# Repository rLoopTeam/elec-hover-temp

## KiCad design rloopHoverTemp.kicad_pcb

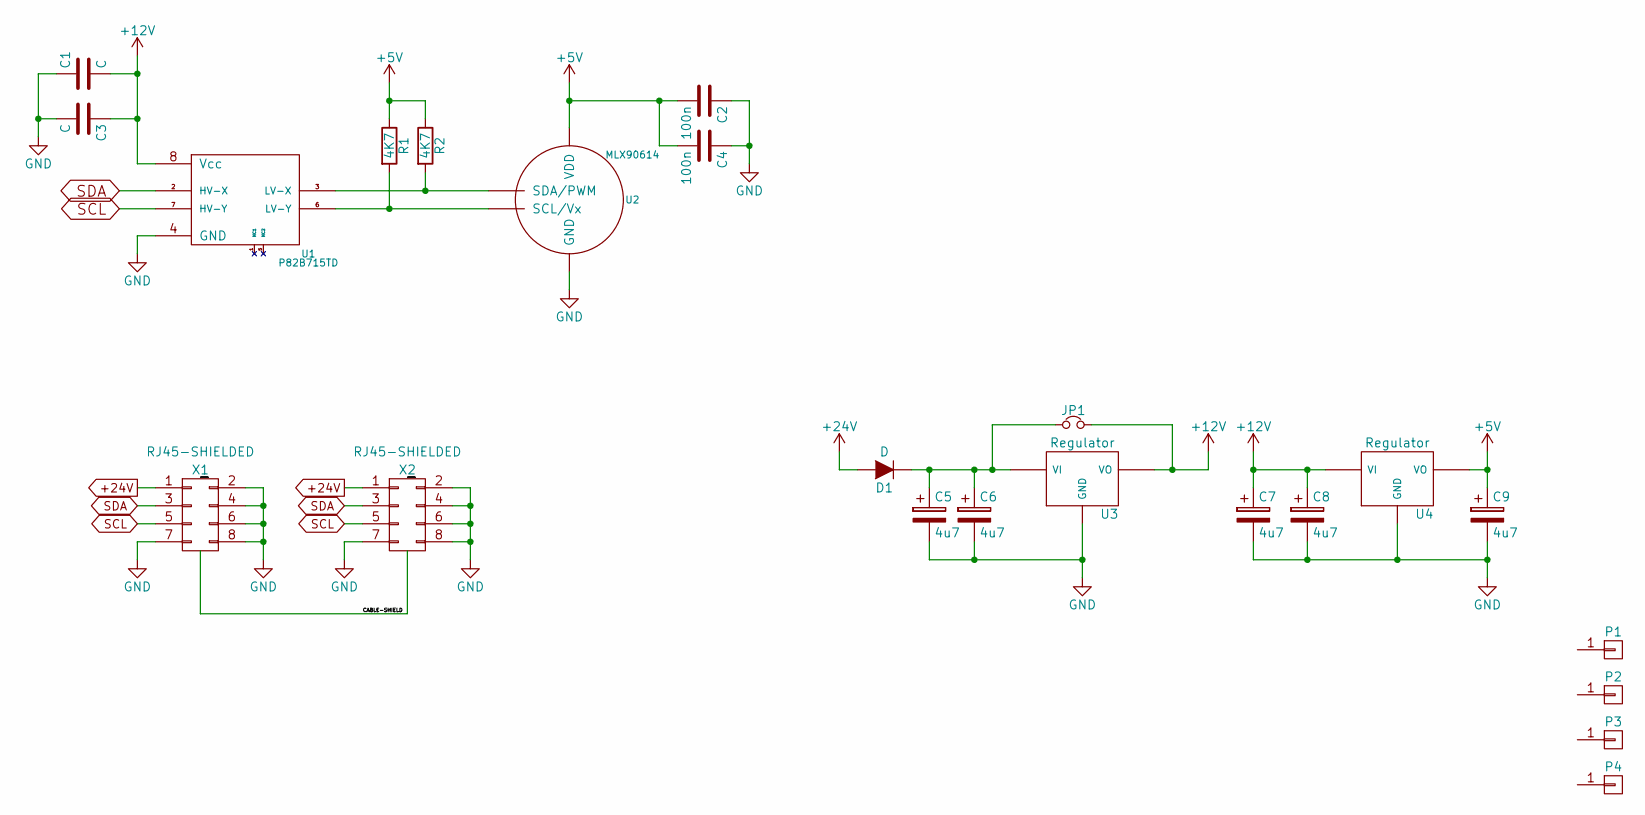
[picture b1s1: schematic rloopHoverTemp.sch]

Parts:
C1, C3: C; C_0603_HandSoldering
C2, C4: 100n; C_0603_HandSoldering
C5, C6, C7, C8, C9: 4u7; C_1206_HandSoldering
D1: D; SOD-123
JP1: Jumper_NC_Small; SOLDERJUMPER
P1, P2, P3, P4: CONN_01X01; SCREWPAD-4-40
R1, R2: 4K7; R_0603_HandSoldering
U1: P82B715TD; SOIC-8_3.9x4.9mm_Pitch1.27mm
U2: MLX90614; TO39
U3, U4: Regulator; SOT89-3-VREG
X1, X2: RJ45-SHIELDED; RJ45-TE-5558342-1

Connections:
+5V: C2.2, C4.2, C9.1, R1.1, R2.1, U2.3 (VDD), U4.VO
+12V: C1.2, C3.1, C7.1, C8.1, JP1.2, U1.8 (Vcc), U3.VO, U4.VI
+24V: D1.2 (A), X1.1, X2.1
/CABLE-SHIELD: X1.SHLD (SHLD1), X2.SHLD (SHLD1)
GND: C1.1, C2.1, C3.2, C4.1, C5.2, C6.2, C7.2, C8.2, C9.2, U1.4 (GND), U2.4 (GND), U3.GND, U4.GND, X1.2, X1.4, X1.6, X1.7, X1.8, X2.2, X2.4, X2.6, X2.7, X2.8
unnamed: C5.1, C6.1, D1.1 (K), JP1.1, U3.VI
unnamed: R1.2, U1.6 (LV-Y), U2.1 (SCL/Vx)
unnamed: R2.2, U1.3 (LV-X), U2.2 (SDA/PWM)
SCL: U1.7 (HV-Y), X1.5, X2.5
SDA: U1.2 (HV-X), X1.3, X2.3

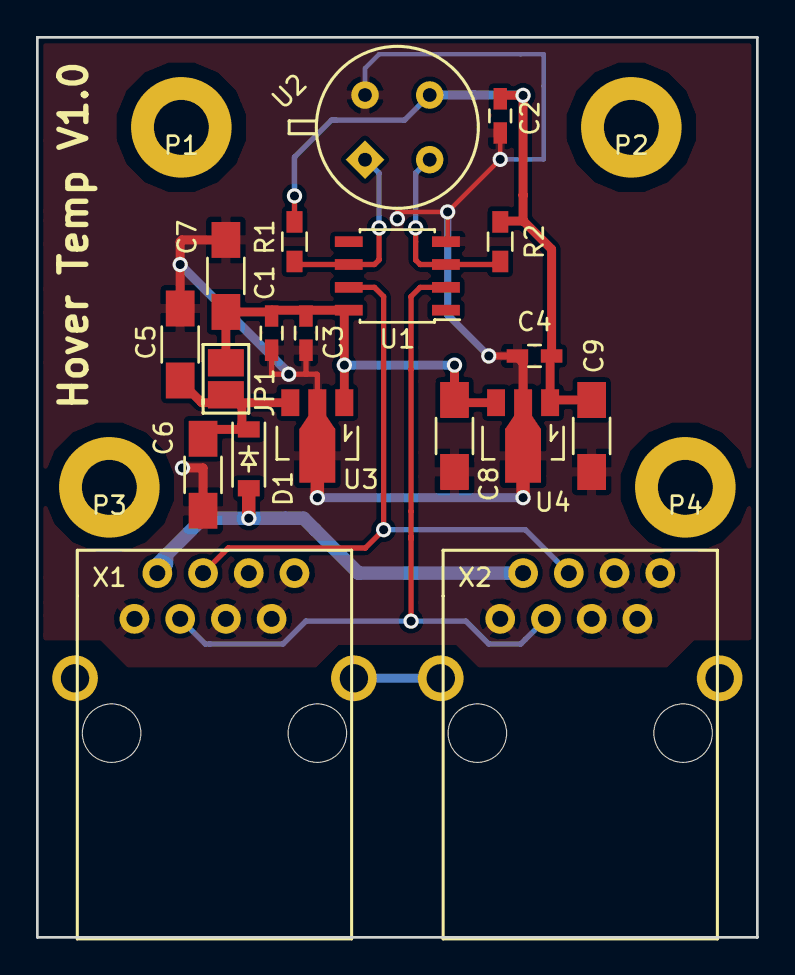
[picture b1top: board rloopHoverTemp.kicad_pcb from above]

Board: 2 copper layers, 40.0 x 50.0 mm, 23 parts (0 on the bottom side), 10 nets.

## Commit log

2016-05-17 first rev
2016-05-17 prelim layout
2016-05-17 more spacing for 24V, better route, gnd'd mnts
2016-05-17 split the grounds
2016-05-17 touchup, put some dimensions on there
2016-05-17 added reverse wiring protection diode
2016-05-21 complete redo with MLX sensor
2016-05-22 dual MNL connector version
2016-05-22 version with dual RJ45 connector
2016-05-22 different shielding scheme for RJ45
2016-05-22 removed grounds from screw holes, added a silk label
2016-05-22 missed two capacitor values
